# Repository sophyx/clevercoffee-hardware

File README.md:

# Fork from [clevercoffee-hardware](https://github.com/rancilio-pid/clevercoffee-hardware)

Forked because I want to improve the routing of the minimal PCB. Original Readme:

# CleverCoffee Hardware 

<br>

KiCAD projects for breakout boards based on the ESP32 DevKitC v4 

* Minimal PCB with a smaller footprint and all unused GPIO-Pins on a separate header
* Development PCB with additional support for rotary encoder and dimmer circuit
* Experimental SMD variant of the minimal PCB with additional headers for the optional brew and steam LEDs
* Experimental SMD variant of the development PCB with a smaller footprint and wider spacing of the headers to be able to mount JST XH plugs

<br>
If you want to order PCBs yourself please keep in mind that the development boards are still a work in progress. The pinmapping for the features that are not yet on the minimal PCB is subject to change at any time.
<br>
<br>
For the latest revision of the minimal PCB just write us a message on our Discord.
<br>
<br>
If you want to create your own hardware based on our designs, please contact us beforehand to make sure you're not developing against an outdated revision. There may be unpublished changes not yet available in the repository.<br>
Also note that for regulatory and safety reasons we are not interested in designs with components operating at mains voltage.
<br>
<br>

<br>
<br>

This work is licensed under a <a rel="license" href="http://creativecommons.org/licenses/by-nc-sa/4.0/">Creative Commons Attribution-NonCommercial-ShareAlike 4.0 International License</a>

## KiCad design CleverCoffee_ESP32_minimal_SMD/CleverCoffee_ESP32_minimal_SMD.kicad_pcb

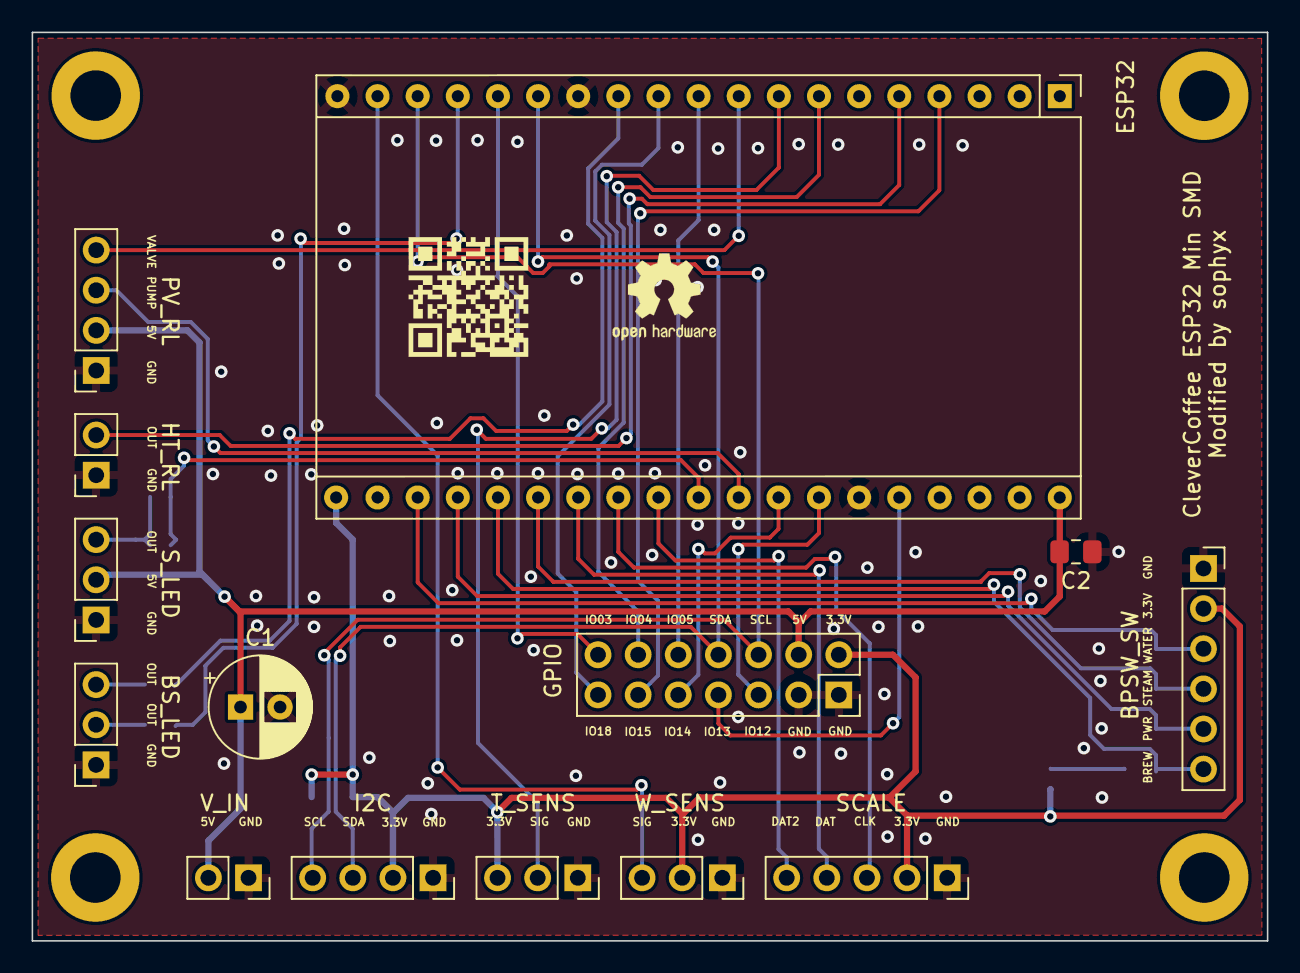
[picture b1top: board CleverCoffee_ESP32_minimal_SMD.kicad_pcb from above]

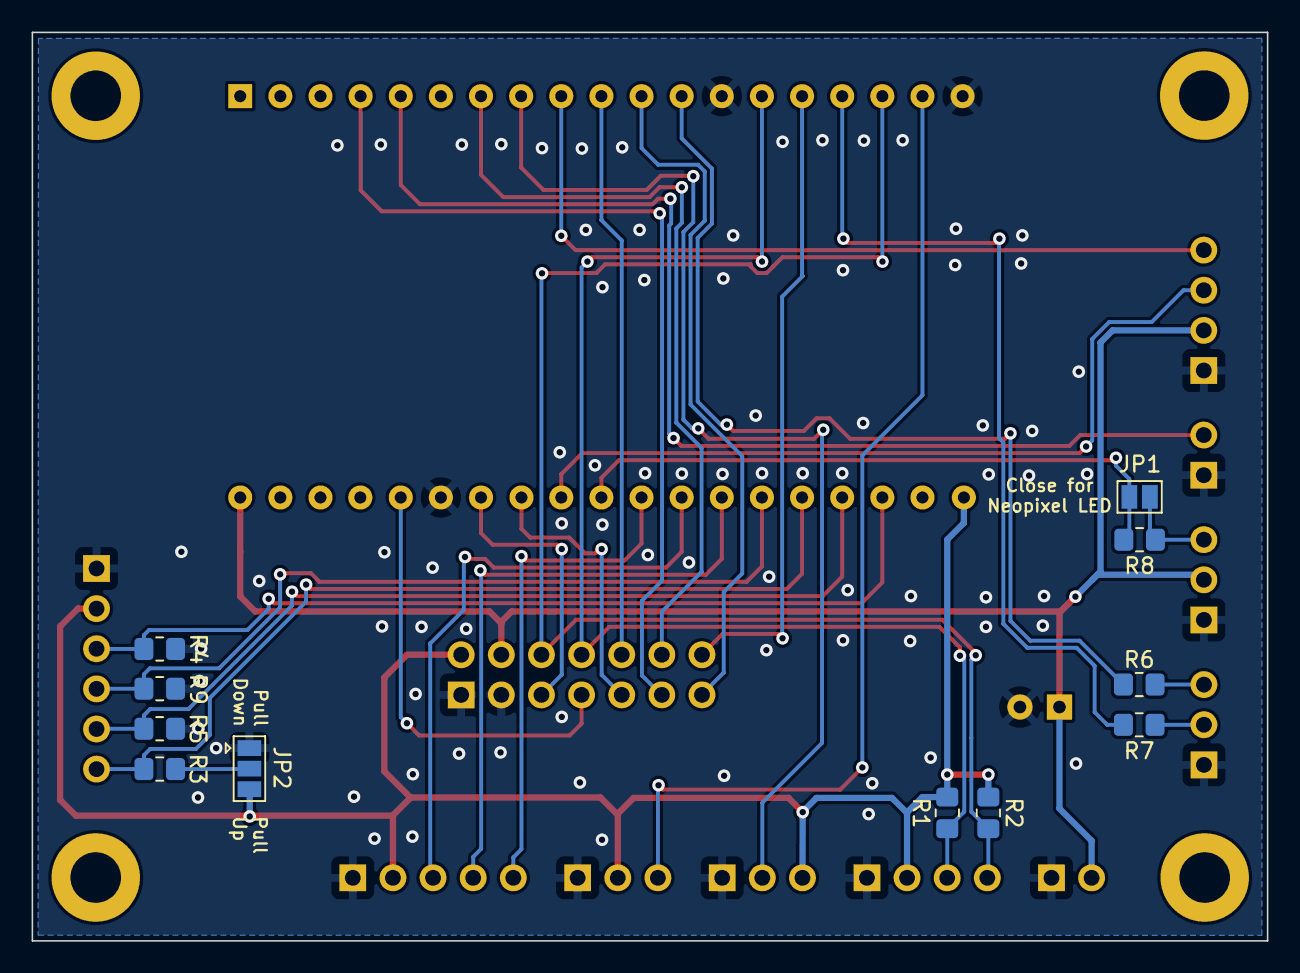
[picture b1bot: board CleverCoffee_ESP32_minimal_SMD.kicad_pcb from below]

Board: 2 copper layers, 78.2 x 57.5 mm, 29 parts (11 on the bottom side), 32 nets.

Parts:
BPSW_SW: Conn_01x05; PinSocket_1x06_P2.54mm_Vertical
BS_LED: Conn_01x02; PinSocket_1x03_P2.54mm_Vertical
C1: 220 μF; CP_Radial_D6.3mm_P2.50mm
C2: 100 nF; C_0805_2012Metric_Pad1.18x1.45mm_HandSolder
ESP32: NodeMCU_DevKitC_v4; NodeMCU DevKitC v4
GPIO: Conn_02x07_Counter_Clockwise; PinSocket_2x07_P2.54mm_Vertical
H1, H2, H3, H4: MountingHole_3.2mm_M3_DIN965_Pad
HT_RL: Conn_01x02; PinSocket_1x02_P2.54mm_Vertical
I2C: Conn_01x04; PinSocket_1x04_P2.54mm_Vertical
JP1: SolderJumper_2_Open; SolderJumper-2_P1.3mm_Open_Pad1.0x1.5mm
JP2: SolderJumper_3_Open; SolderJumper-3_P1.3mm_Open_Pad1.0x1.5mm
PV_RL: Conn_01x04; PinSocket_1x04_P2.54mm_Vertical
R1, R2: 4K7 Ω; R_0805_2012Metric_Pad1.20x1.40mm_HandSolder
R3, R4, R5, R9: 47K Ω; R_0805_2012Metric_Pad1.20x1.40mm_HandSolder
R6, R7, R8: 220 Ω; R_0805_2012Metric_Pad1.20x1.40mm_HandSolder
SCALE: Conn_01x05; PinSocket_1x05_P2.54mm_Vertical
S_LED: Conn_01x03; PinSocket_1x03_P2.54mm_Vertical
T_SENS: Conn_01x03; PinSocket_1x03_P2.54mm_Vertical
V_IN: Conn_01x02; PinSocket_1x02_P2.54mm_Vertical
W_SENS: Conn_01x03; PinSocket_1x03_P2.54mm_Vertical

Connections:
+3V3: BPSW_SW.2, ESP32.20 (3V3), GPIO.2, I2C.2, JP2.3 (B), R1.2, R2.2, SCALE.2, T_SENS.3, W_SENS.2
+5V: C1.1, C2.1, ESP32.38 (VDD), GPIO.4, PV_RL.2, S_LED.2, V_IN.2
CLK: ESP32.27 (IO33), SCALE.3
DAT: ESP32.26 (IO32), SCALE.4
DAT2: ESP32.28 (IO25), SCALE.5
GND: BPSW_SW.1, BS_LED.1, C1.2, C2.2, ESP32.13 (GND), ESP32.19 (GND), ESP32.33 (GND), GPIO.1, GPIO.3, HT_RL.1, I2C.1, JP2.1 (A), PV_RL.1, R4.2, R5.1, R9.2, SCALE.1, S_LED.1, T_SENS.1, V_IN.1, W_SENS.1
IO1: ESP32.16 (IO1/Tx), R7.2
IO2: ESP32.5 (IO2), HT_RL.2
IO3: ESP32.15 (IO3/Rx), GPIO.14
IO4: ESP32.7 (IO4), GPIO.12
IO5: ESP32.10 (IO5), GPIO.10
IO12: ESP32.32 (IO12/TDI), GPIO.5
IO13: ESP32.34 (IO13/TCK), GPIO.7
IO14: ESP32.31 (IO14/TMS), GPIO.9
IO15: ESP32.4 (IO15/TDO), GPIO.11
IO16: ESP32.8 (IO16/Rx2), T_SENS.2
IO18: ESP32.11 (IO18), GPIO.13
IO19: ESP32.12 (IO19), R6.2
IO23: ESP32.18 (IO23), W_SENS.3
IO26: ESP32.29 (IO26), JP1.2 (B), R8.2
IO34: BPSW_SW.6, ESP32.24 (IO34), R3.2
IO35: BPSW_SW.4, ESP32.25 (IO35), R9.1
IO36: BPSW_SW.3, ESP32.22 (IO36), R4.1
IO39: BPSW_SW.5, ESP32.23 (IO39), R5.2
unnamed: BS_LED.2, R7.1
unnamed: BS_LED.3, R6.1
unnamed: JP1.1 (A), R8.1, S_LED.3
unnamed: JP2.2 (C), R3.1
PUMP: ESP32.30 (IO27), PV_RL.3
SCL: ESP32.17 (IO22/SCL), GPIO.6, I2C.4, R2.1
SDA: ESP32.14 (IO21/SDA), GPIO.8, I2C.3, R1.1
VALVE: ESP32.9 (IO17/Tx2), PV_RL.4

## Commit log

2024-01-28 changed README and .gitignore
2024-01-28 mirrored pin headers to correct GND pad, changed SMD footprints to 0805 and rearranged SMD parts
2024-01-28 fixed errors in .gitignore
2024-01-30 first routing draft
2024-02-08 improved routing, added gnd plane stitching

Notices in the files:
README.md:
Creative Commons Licence
CC BY-NC-SA 4.0
